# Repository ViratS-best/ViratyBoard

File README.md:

# ViratyBoard

A RP2040 board! My second-ever PCB!!!

I made this devboard because I really wanted to learn how to integrate a chip, and maybe later I could make compute modules with this knowledge! I know this is really basic compared to a 6-8 layer chip CM, but it's a start I hope to build on! 

This is mainly built using the RP2040 datasheet and this guide: https://github.com/KaiPereira/build-a-devboard

## What makes my devboard unique?

* **Battery & USB** Accepts both USB power and a battery connection!

# How I built it:

I started by looking over the build-a-devboard GitHub repository, and I followed the guide as well.

Next, I looked over the datasheet for the RP2040, hopefully to find the same image the GitHub repository referenced that showed the result.

So I started developing the board.

First, I set up the decoupling capacitors:

Then I continued by labling the whole RP2040:

I also added the USB power source and programmer:

Then I added the crystal oscillator to make the RP2040 actually work:

As well as the flash storage:

And lastly made the pin headers:

OH NO!!!

I kept the wrong voltage regulator!!

Thankfully it was an easy fix:

But then I thought I should also add something original, like battery power instead of USB... so I added that:

So... now it accepts both BATTERY AND USB!!!

Plug in BOTH: The USB power instantly turns the MOSFET OFF, completely disconnecting the AA batteries so they don't get accidentally charged or drained!

Next I attached all the footprints:

and looked at my final schematic:

Only routing and PCB design left!

Now this is where it got hard...

## Where did I get stuck at?

This devboard is 4 layers... It's not 2, because, due to the battery mechanism, routing it in 2 layers became really hard and complicated, so I had to switch to 4 layers. This could be done in 2 layers, but I just couldn't manage to, and I was really confused about how to do it, so I was stuck with this. **I asked about routing on Reddit**:

This was a place where I got stuck during 2-layer routing:

And another place I got stuck at:

So it became a 4-Layer project:

I finally made good progress:

But I ran into an issue on one of the last things:

So I fixed it using:

Then I filled for Signal & for Ground on the other two layers!

Just like that I am **DONE**!

## Project Structure

```text
README.md
devboard.kicad_pcb
devboard.kicad_pro
devboard.kicad_sch
devboard.zip    # Gerber
bom.csv
submit.ino
```

## BOM:

| Part | Qty | Unit | Total | Vendor |
| ---- | ----- | ----- | ----- | ---- |
| [PCB Devboard] | 1 | $66.63 | $66.63 | [JLCPCB](https://www.jlcpcb.com) |
| Tax & shipping for the whole order |  |  | $0.05 |  |
| **Total** | | | **$66.68** | |

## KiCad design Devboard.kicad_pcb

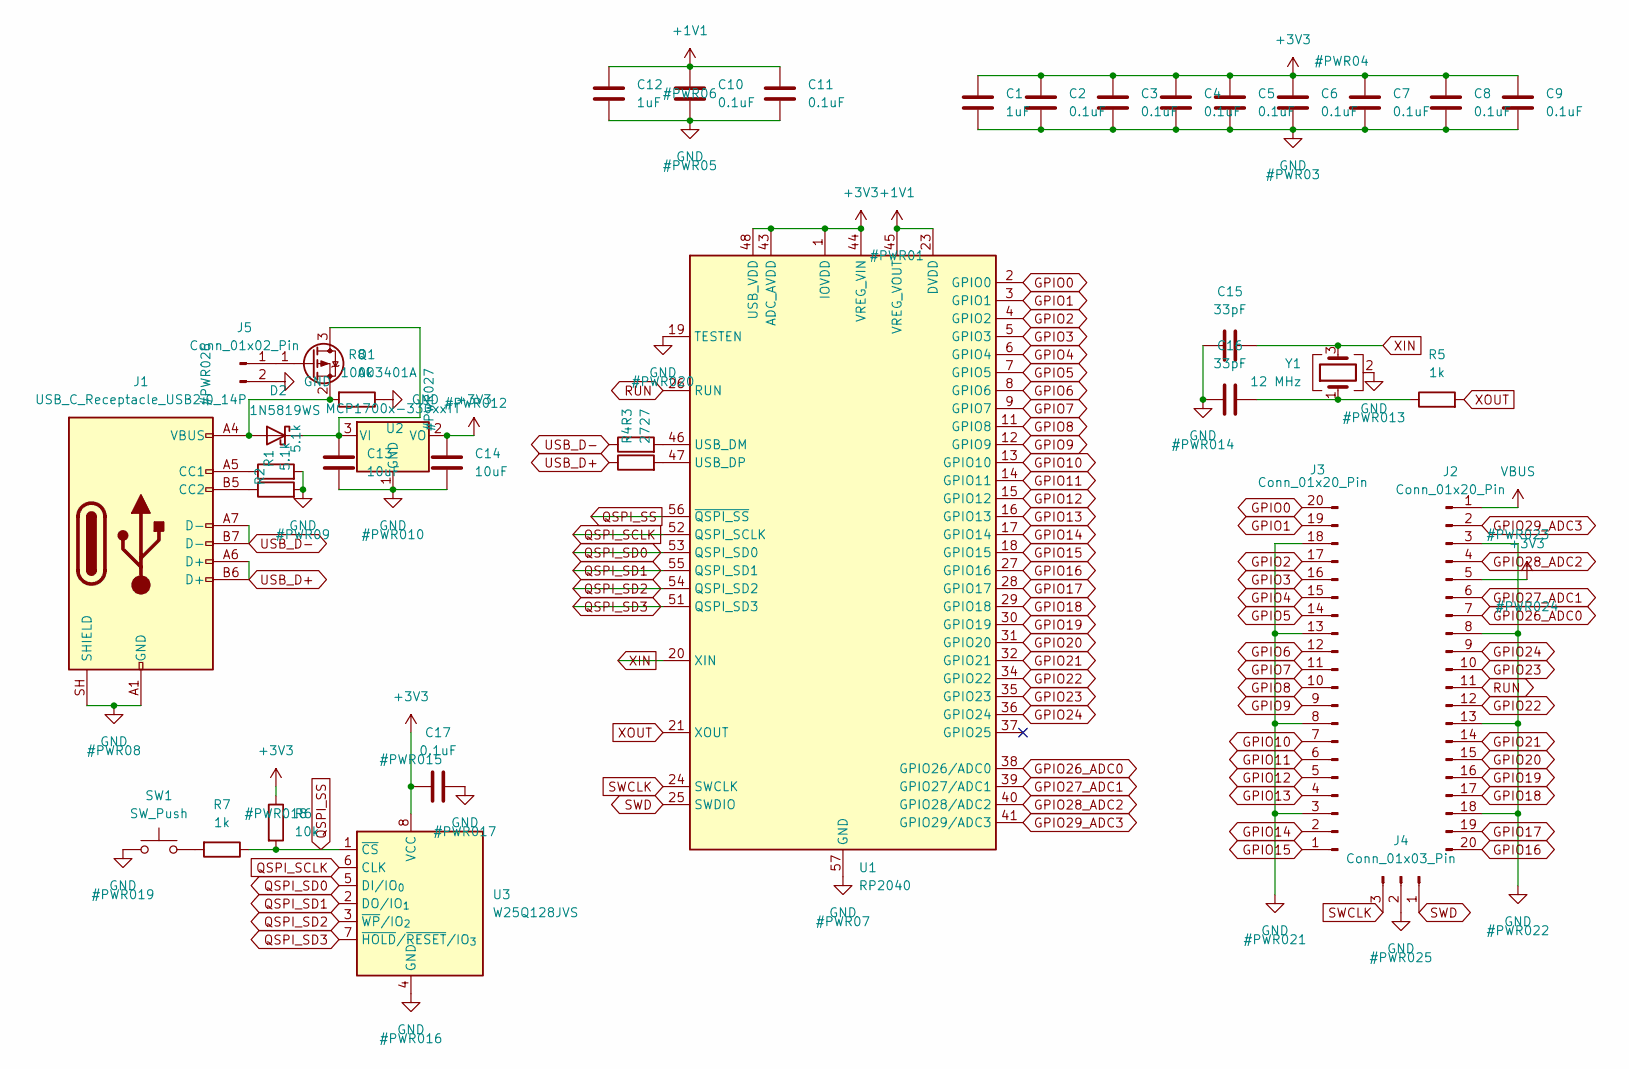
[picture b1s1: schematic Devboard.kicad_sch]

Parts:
C1, C12: 1uF; C_0402_1005Metric
C2, C3, C4, C5, C6, C7, C8, C9, C10, C11, C17: 0.1uF; C_0402_1005Metric
C13, C14: 10uF; C_0603_1608Metric
C15, C16: 33pF; C_0402_1005Metric
D2: 1N5819WS; D_SOD-323
J1: USB_C_Receptacle_USB2.0_14P; USB_C_Receptacle_HRO_TYPE-C-31-M-12
J2, J3: Conn_01x20_Pin; PinHeader_1x20_P2.54mm_Vertical
J4: Conn_01x03_Pin; PinHeader_1x03_P2.54mm_Vertical
J5: Conn_01x02_Pin; PinHeader_1x02_P2.54mm_Vertical
Q1: AO3401A; SOT-23
R1, R2: 5.1k; R_0402_1005Metric
R3, R4: 27; R_0402_1005Metric
R5, R7: 1k; R_0402_1005Metric
R6: 10k; R_0402_1005Metric
R8: 100k; R_0603_1608Metric
SW1: SW_Push; SW_Push_SPST_NO_Alps_SKRK
U1: RP2040; QFN-56-1EP_7x7mm_P0.4mm_EP3.2x3.2mm
U2: MCP1700x-330xxTT; SOT-23
U3: W25Q128JVS; SOIC-8_5.3x5.3mm_P1.27mm
Y1: 12 MHz; Crystal_SMD_3225-4Pin_3.2x2.5mm

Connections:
+1V1: C10.1, C11.1, C12.1, U1.23 (DVDD), U1.45 (VREG_VOUT), U1.50 (DVDD)
+3V3: C1.1, C2.1, C3.1, C4.1, C5.1, C6.1, C7.1, C8.1, C9.1, C14.1, C17.2, J2.5, R6.1, U1.1 (IOVDD), U1.10 (IOVDD), U1.22 (IOVDD), U1.33 (IOVDD), U1.42 (IOVDD), U1.43 (ADC_AVDD), U1.44 (VREG_VIN), U1.48 (USB_VDD), U1.49 (IOVDD), U2.2 (VO), U3.8 (VCC)
GND: C1.2, C2.2, C3.2, C4.2, C5.2, C6.2, C7.2, C8.2, C9.2, C10.2, C11.2, C12.2, C13.2, C14.2, C15.2, C16.2, C17.1, J1.A1 (GND), J1.A12 (GND), J1.B1 (GND), J1.B12 (GND), J1.SH (SHIELD), J2.3, J2.8, J2.13, J2.18, J3.3, J3.8, J3.13, J3.18, J4.2, J5.2, R1.2, R2.2, R8.1, SW1.1, U1.19 (TESTEN), U1.57 (GND), U2.1 (GND), U3.4 (GND), Y1.2 (G), Y1.4 (G)
GPIO0: J3.20, U1.2 (GPIO0)
GPIO1: J3.19, U1.3 (GPIO1)
GPIO2: J3.17, U1.4 (GPIO2)
GPIO3: J3.16, U1.5 (GPIO3)
GPIO4: J3.15, U1.6 (GPIO4)
GPIO5: J3.14, U1.7 (GPIO5)
GPIO6: J3.12, U1.8 (GPIO6)
GPIO7: J3.11, U1.9 (GPIO7)
GPIO8: J3.10, U1.11 (GPIO8)
GPIO9: J3.9, U1.12 (GPIO9)
GPIO10: J3.7, U1.13 (GPIO10)
GPIO11: J3.6, U1.14 (GPIO11)
GPIO12: J3.5, U1.15 (GPIO12)
GPIO13: J3.4, U1.16 (GPIO13)
GPIO14: J3.2, U1.17 (GPIO14)
GPIO15: J3.1, U1.18 (GPIO15)
GPIO16: J2.20, U1.27 (GPIO16)
GPIO17: J2.19, U1.28 (GPIO17)
GPIO18: J2.17, U1.29 (GPIO18)
GPIO19: J2.16, U1.30 (GPIO19)
GPIO20: J2.15, U1.31 (GPIO20)
GPIO21: J2.14, U1.32 (GPIO21)
GPIO22: J2.12, U1.34 (GPIO22)
GPIO23: J2.10, U1.35 (GPIO23)
GPIO24: J2.9, U1.36 (GPIO24)
GPIO26_ADC0: J2.7, U1.38 (GPIO26/ADC0)
GPIO27_ADC1: J2.6, U1.39 (GPIO27/ADC1)
GPIO28_ADC2: J2.4, U1.40 (GPIO28/ADC2)
GPIO29_ADC3: J2.2, U1.41 (GPIO29/ADC3)
unnamed: C16.1, R5.1, Y1.1
unnamed: D2.2 (A), J1.A4 (VBUS), J1.A9 (VBUS), J1.B4 (VBUS), J1.B9 (VBUS), Q1.2 (S), R8.2
unnamed: C13.1, D2.1 (K), Q1.3 (D), U2.3 (VI)
unnamed: J1.A5 (CC1), R1.1
unnamed: J1.B5 (CC2), R2.1
unnamed: J5.1, Q1.1 (G)
unnamed: R7.2, SW1.2
unnamed: R3.2, U1.46 (USB_DM)
unnamed: R4.2, U1.47 (USB_DP)
QSPI_SCLK: U1.52 (QSPI_SCLK), U3.6 (CLK)
QSPI_SD0: U1.53 (QSPI_SD0), U3.5 (DI/IO_{0})
QSPI_SD1: U1.55 (QSPI_SD1), U3.2 (DO/IO_{1})
QSPI_SD2: U1.54 (QSPI_SD2), U3.3 (~WP/IO_{2})
QSPI_SD3: U1.51 (QSPI_SD3), U3.7 (~HOLD/~RESET/IO_{3})
QSPI_SS: R6.2, R7.1, U1.56 (~QSPI_SS), U3.1 (~CS)
RUN: J2.11, U1.26 (RUN)
SWCLK: J4.3, U1.24 (SWCLK)
SWD: J4.1, U1.25 (SWDIO)
USB_D+: J1.A6 (D+), J1.B6 (D+), R4.1
USB_D-: J1.A7 (D-), J1.B7 (D-), R3.1
VBUS: J2.1
XIN: C15.1, U1.20 (XIN), Y1.3
XOUT: R5.2, U1.21 (XOUT)

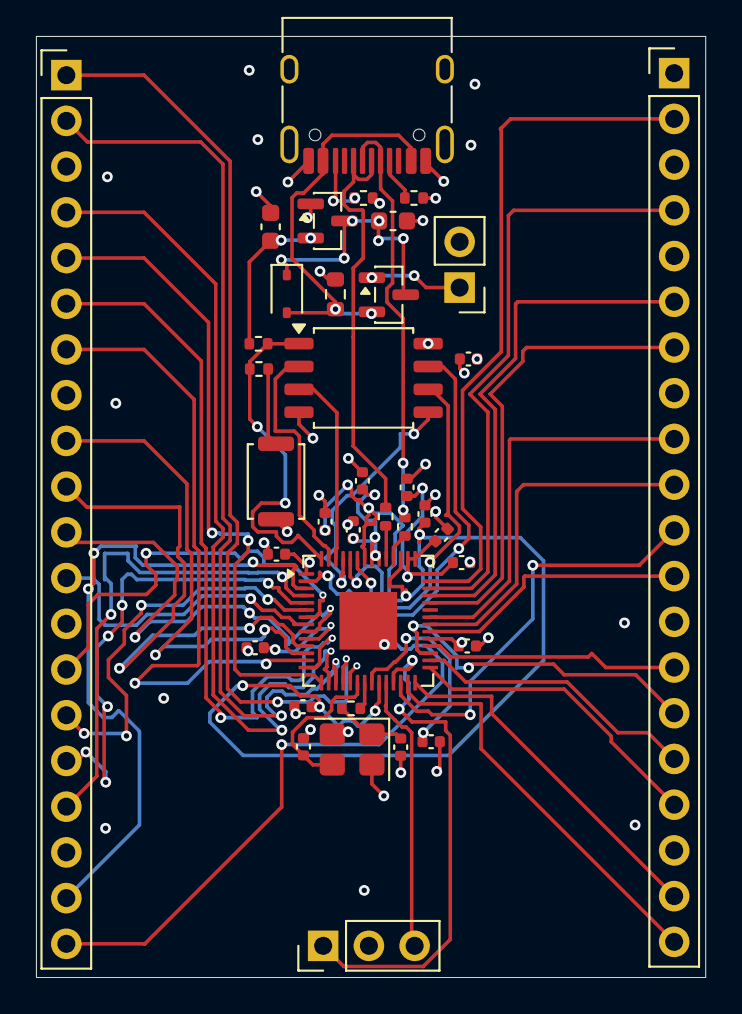
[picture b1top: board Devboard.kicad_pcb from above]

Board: 4 copper layers, 37.2 x 52.3 mm, 37 parts (0 on the bottom side), 54 nets.

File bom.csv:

Designator,Footprint,Quantity,Value,LCSC Part #
"C1, C12",0402,2,1uF,
"C10, C11, C17, C2, C3, C4, C5, C6, C7, C8, C9",0402,11,0.1uF,
"C13, C14",0603,2,10uF,
"C15, C16",0402,2,33pF,
D2,D_SOD-323,1,1N5819WS,
J1,USB_C_Receptacle_HRO_TYPE-C-31-M-12,1,USB_C_Receptacle_USB2.0_14P,
"J2, J3",PinHeader_1x20_P2.54mm_Vertical,2,Conn_01x20_Pin,
J4,PinHeader_1x03_P2.54mm_Vertical,1,Conn_01x03_Pin,
J5,PinHeader_1x02_P2.54mm_Vertical,1,Conn_01x02_Pin,
Q1,SOT-23,1,AO3401A,
"R1, R2",0402,2,5.1k,
"R3, R4",0402,2,27,
"R5, R7",0402,2,1k,
R6,0402,1,10k,
R8,0603,1,100k,
SW1,SW_Push_SPST_NO_Alps_SKRK,1,SW_Push,
U1,QFN-56-1EP_7x7mm_P0.4mm_EP3.2x3.2mm,1,RP2040,
U2,SOT-23,1,MCP1700x-330xxTT,
U3,SOIC-8_5.3x5.3mm_P1.27mm,1,W25Q128JVS,
Y1,Crystal_SMD_3225-4Pin_3.2x2.5mm,1,12 MHz,
